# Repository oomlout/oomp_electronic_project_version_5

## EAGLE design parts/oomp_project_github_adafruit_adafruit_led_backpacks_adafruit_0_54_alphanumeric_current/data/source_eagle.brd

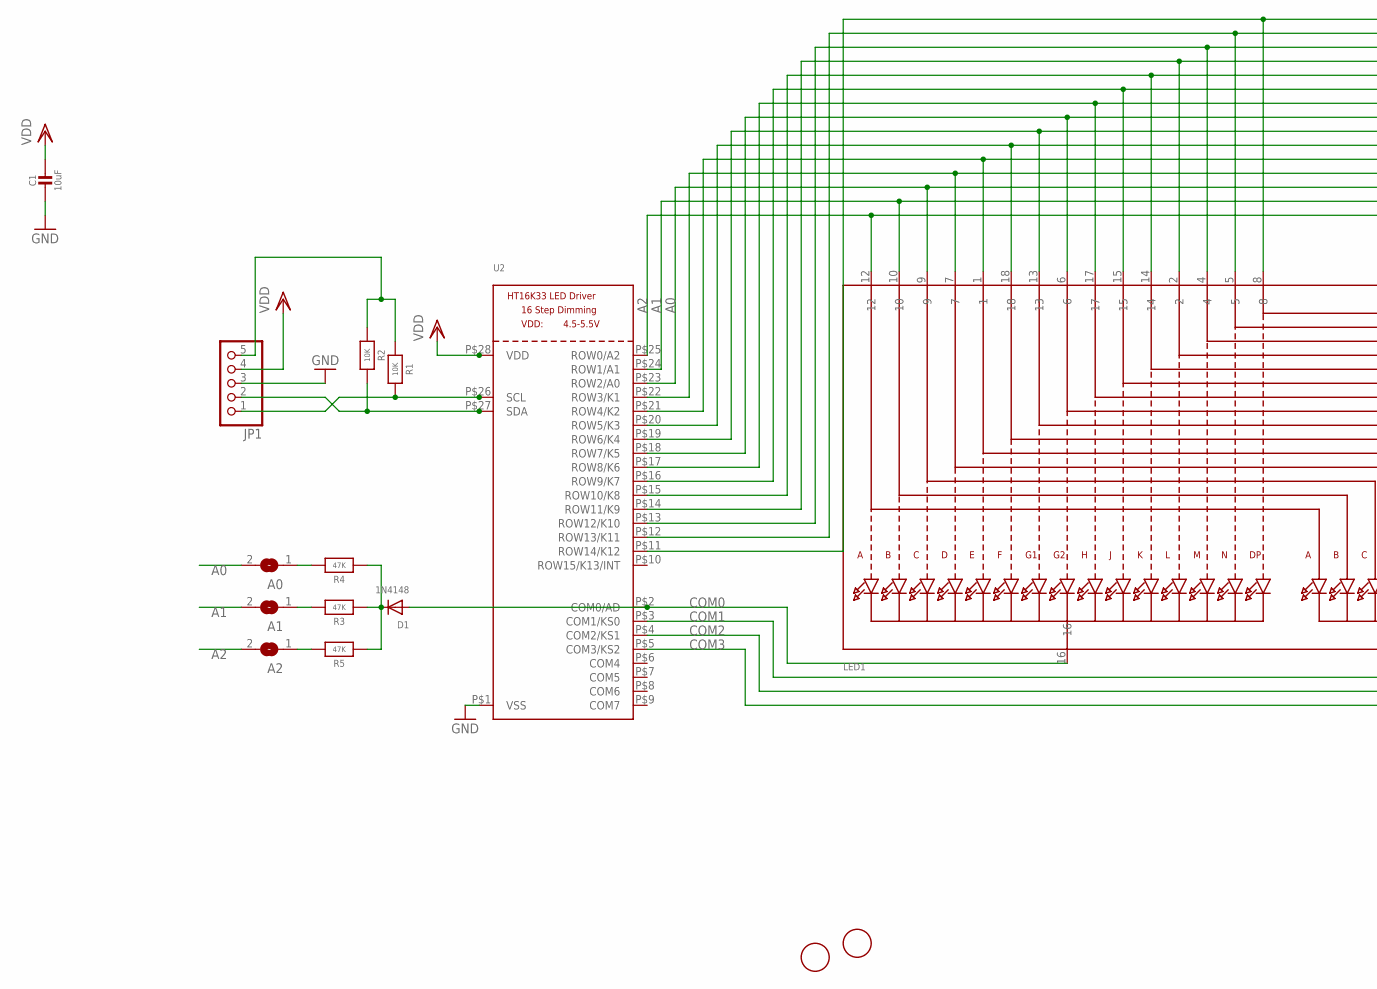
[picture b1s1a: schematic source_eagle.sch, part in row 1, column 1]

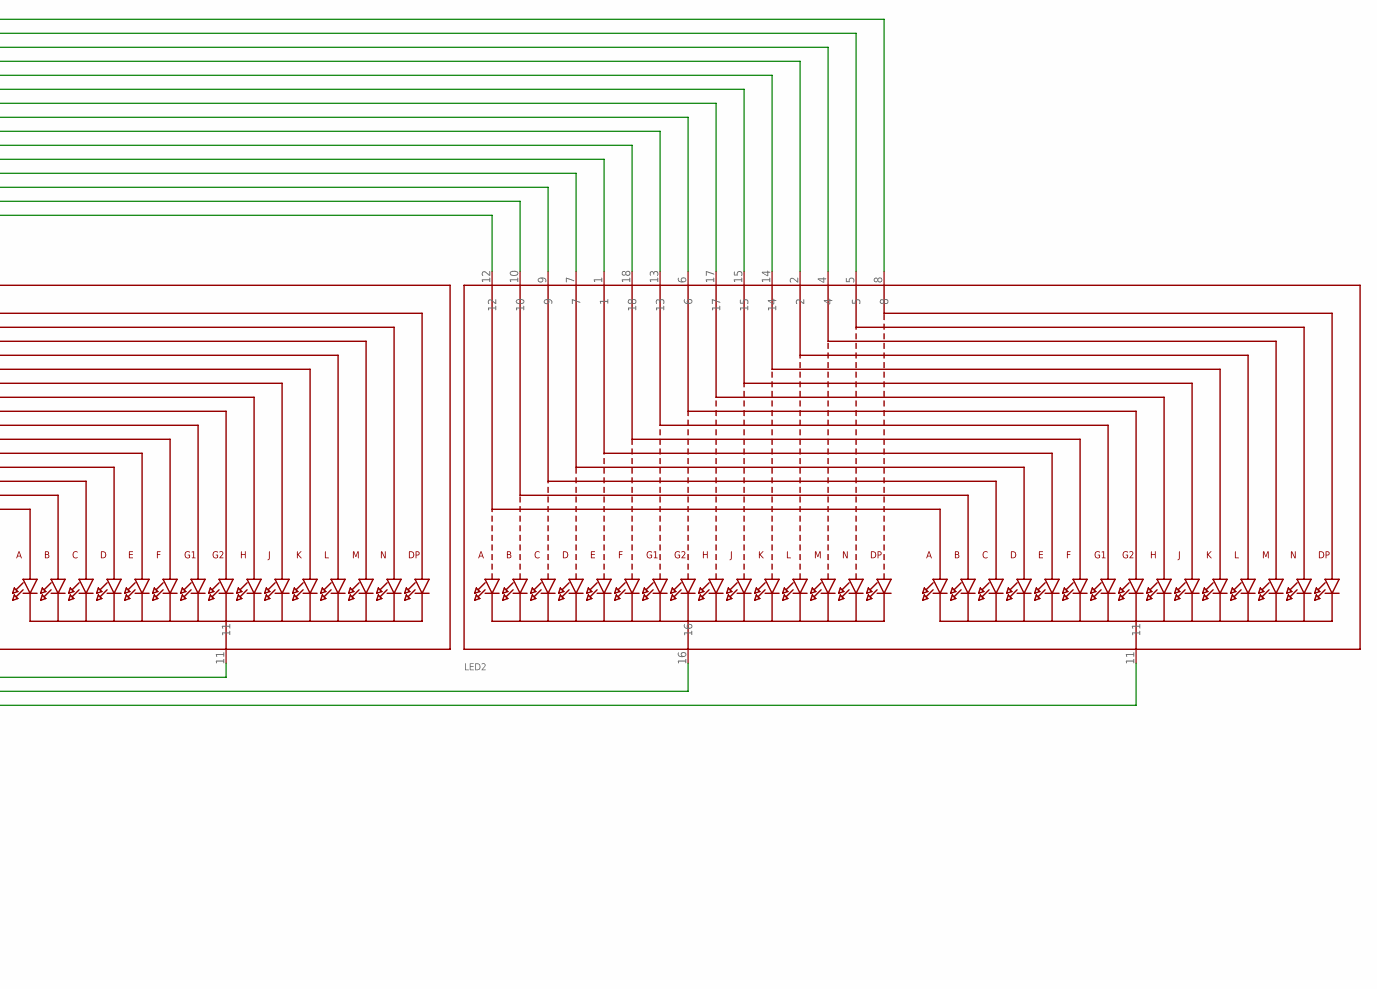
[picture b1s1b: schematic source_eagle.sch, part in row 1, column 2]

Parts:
A0, A1, A2: SOLDERJUMPERREFLOW_NOPASTE; SOLDERJUMPER_REFLOW_NOPASTE
C1: 10uF; 0805-NO
D1: 1N4148; SOD-323F
JP1: HEADER-1X570MIL; 1X05_ROUND_70
LED1, LED2: DISP_SEGMENT_STARBURST_DUAL_COMMONCATHODE; SEGMENT_STARTBUST_DUAL_KWA-541CBB
R1, R2: 10K; 0805-NO
R3, R4, R5: 47K; 0805-NO
U2: HT16K33_SOP28; SOP28_300MIL
U$1, U$2: FIDUCIAL; FIDUCIAL_1MM

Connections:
A0: A0.2, LED1.9, LED2.9, U2.P$23 (ROW2/A0)
A1: A1.2, LED1.10, LED2.10, U2.P$24 (ROW1/A1)
A2: A2.2, LED1.12, LED2.12, U2.P$25 (ROW0/A2)
COM0: D1.A, LED1.16, U2.P$2 (COM0/AD)
COM1: LED1.11, U2.P$3 (COM1/KS0)
COM2: LED2.16, U2.P$4 (COM2/KS1)
COM3: LED2.11, U2.P$5 (COM3/KS2)
GND: C1.2, JP1.3, U2.P$1 (VSS)
unnamed: D1.C, R3.1, R4.1, R5.1
unnamed: JP1.5, R1.1, R2.1
unnamed: LED1.17, LED2.17, U2.P$17 (ROW8/K6)
unnamed: LED1.15, LED2.15, U2.P$16 (ROW9/K7)
unnamed: LED1.14, LED2.14, U2.P$15 (ROW10/K8)
unnamed: A2.1, R5.2
unnamed: LED1.2, LED2.2, U2.P$14 (ROW11/K9)
unnamed: LED1.4, LED2.4, U2.P$13 (ROW12/K10)
unnamed: LED1.7, LED2.7, U2.P$22 (ROW3/K1)
unnamed: LED1.1, LED2.1, U2.P$21 (ROW4/K2)
unnamed: LED1.18, LED2.18, U2.P$20 (ROW5/K3)
unnamed: LED1.13, LED2.13, U2.P$19 (ROW6/K4)
unnamed: LED1.5, LED2.5, U2.P$12 (ROW13/K11)
unnamed: LED1.8, LED2.8, U2.P$11 (ROW14/K12)
unnamed: LED1.6, LED2.6, U2.P$18 (ROW7/K5)
unnamed: A1.1, R3.2
unnamed: A0.1, R4.2
SCL: JP1.1, R1.2, U2.P$26 (SCL)
SDA: JP1.2, R2.2, U2.P$27 (SDA)
VDD: C1.1, JP1.4, U2.P$28 (VDD)

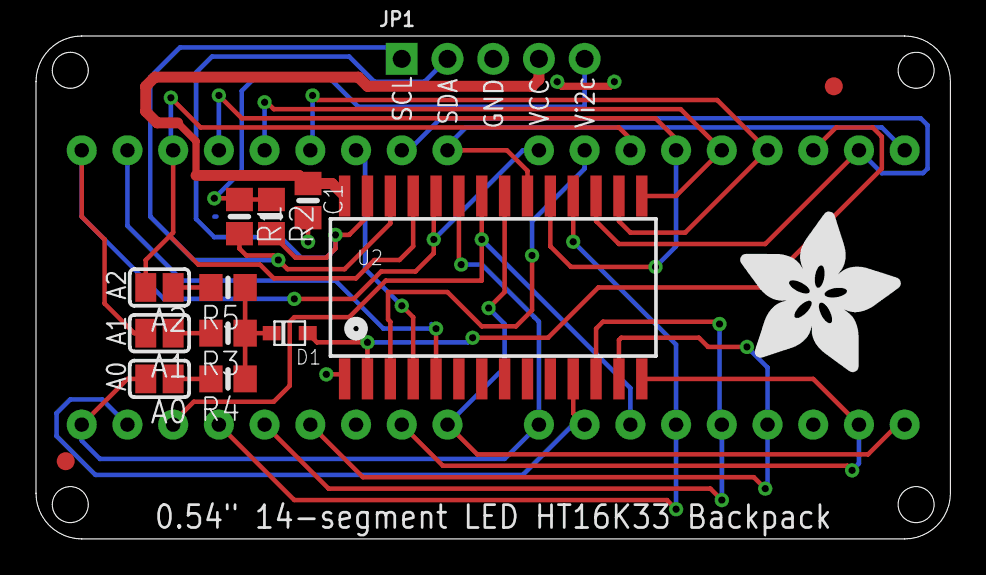
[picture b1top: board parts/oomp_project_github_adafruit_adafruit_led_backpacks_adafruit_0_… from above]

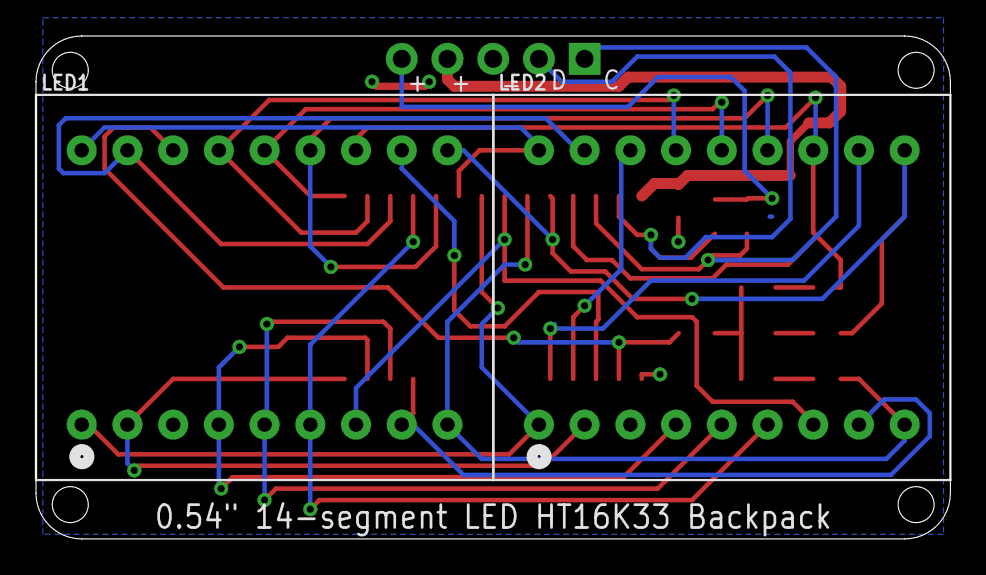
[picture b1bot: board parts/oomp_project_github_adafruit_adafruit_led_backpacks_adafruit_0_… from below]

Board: 2 copper layers, 50.8 x 27.9 mm, 17 parts (2 on the bottom side), 28 nets.

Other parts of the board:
U$3: ADAFRUIT_9MM

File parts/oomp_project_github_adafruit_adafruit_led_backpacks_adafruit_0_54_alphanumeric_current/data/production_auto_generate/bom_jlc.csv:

Comment,Designator,Footprint,LCSC Part #
,JP1,Adafruit 0.54 Alphanumeric v0.1-import-fps:1X05_ROUND_70,C42431835
,U$3,Adafruit 0.54 Alphanumeric v0.1-import-fps:ADAFRUIT_9MM,
,"LED1,LED2",Adafruit 0.54 Alphanumeric v0.1-import-fps:SEGMENT_STARTBUST_DUAL_KWA-541CBB,
,"A0,A1,A2",Adafruit 0.54 Alphanumeric v0.1-import-fps:SOLDERJUMPER_REFLOW_NOPASTE,
,U2,Adafruit 0.54 Alphanumeric v0.1-import-fps:SOP28_300MIL,
10K,"R1,R2",Adafruit 0.54 Alphanumeric v0.1-import-fps:0805-NO,C17414
10uF,C1,Adafruit 0.54 Alphanumeric v0.1-import-fps:0805-NO,
1N4148,D1,Adafruit 0.54 Alphanumeric v0.1-import-fps:SOD-323F,
47K,"R3,R4,R5",Adafruit 0.54 Alphanumeric v0.1-import-fps:0805-NO,C17713
FIDUCIAL,"U$1,U$2",Adafruit 0.54 Alphanumeric v0.1-import-fps:FIDUCIAL_1MM,

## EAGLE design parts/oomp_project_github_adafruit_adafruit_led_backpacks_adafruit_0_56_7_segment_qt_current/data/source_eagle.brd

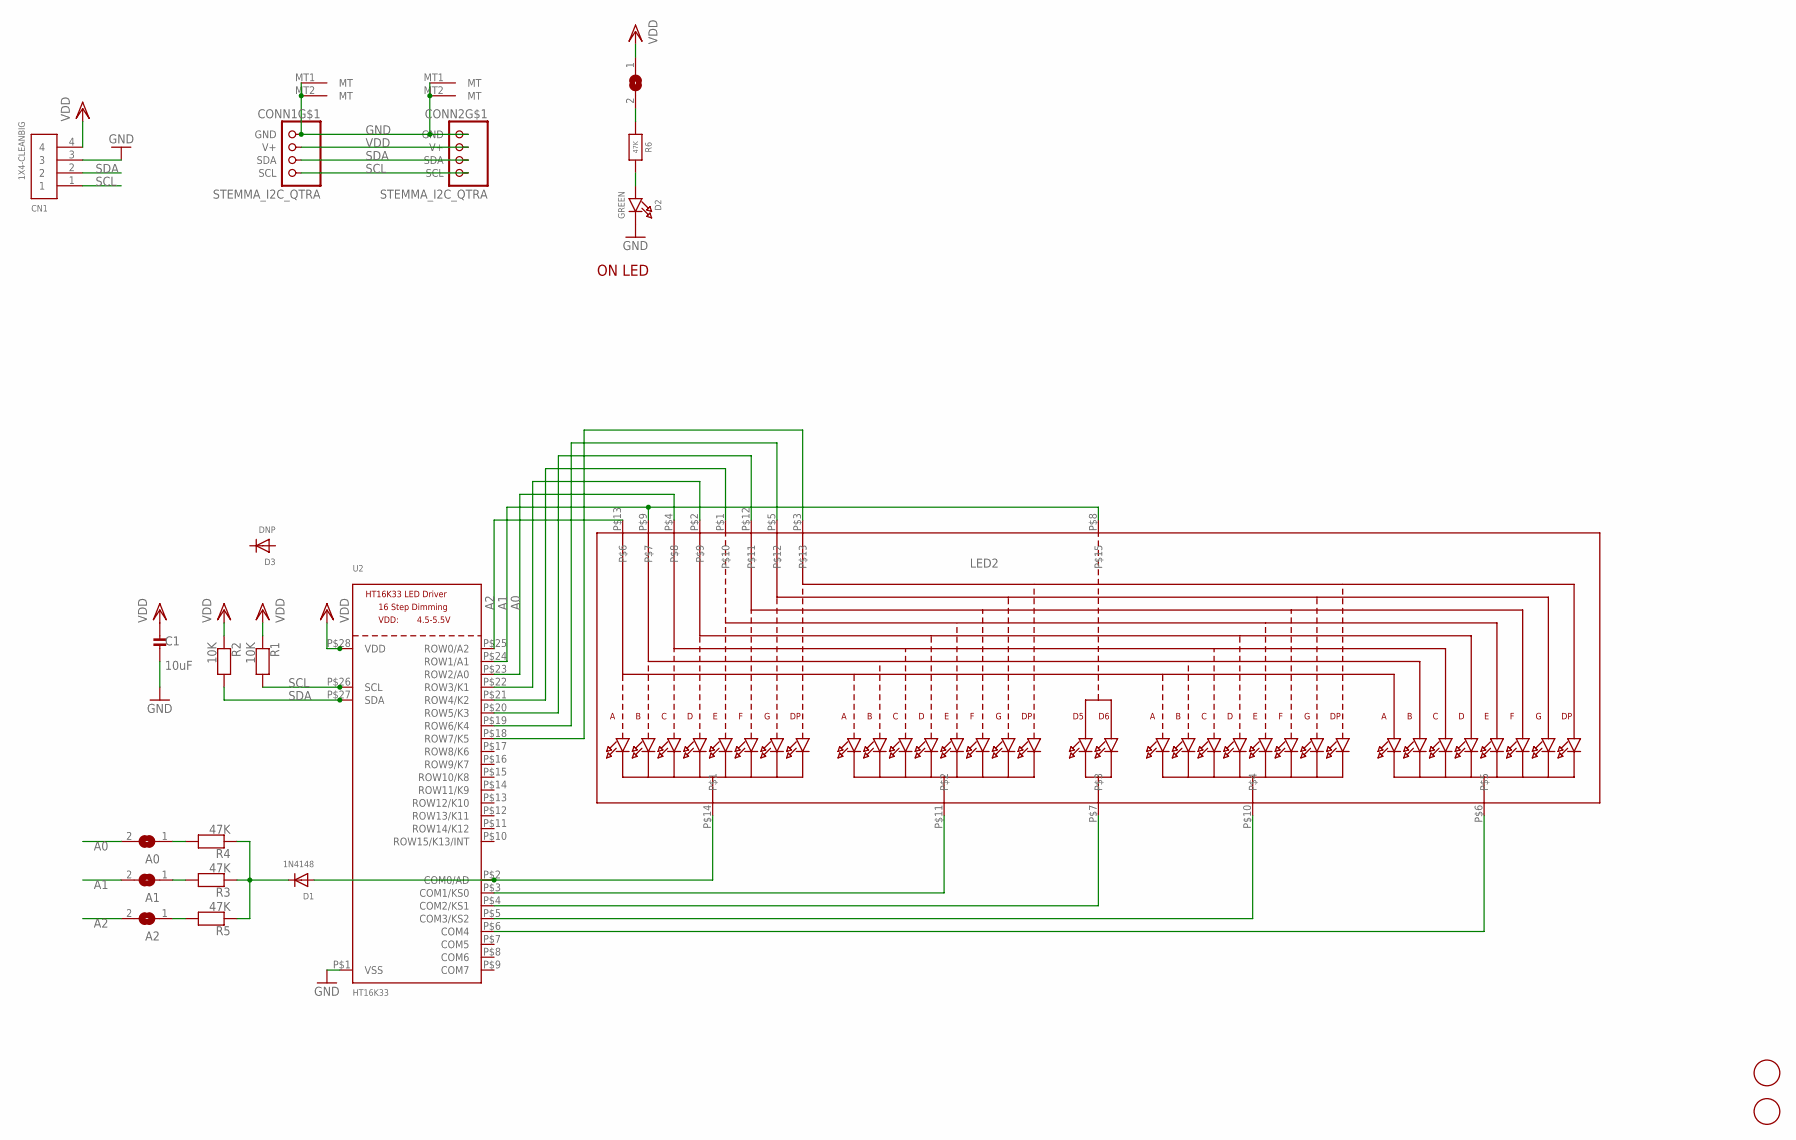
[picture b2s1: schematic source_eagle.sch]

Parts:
A0, A1, A2: SOLDERJUMPER; SOLDERJUMPER_ARROW_NOPASTE
C1: 10uF; 0805_10MGAP
CN1: 1X4-CLEANBIG; 1X04-CLEANBIG
CONN1, CONN2: STEMMA_I2C_QTRA; JST_SH4_RA
D1: 1N4148; SOD-323F
D2: GREEN; CHIPLED_0603_NOOUTLINE
D3: DNP; SOD-323F
LED2: DISP_SEGMENT_4DIGIT_BL-Q56C43; SEGMENT-BL-Q56C43
LEDJMP: SOLDERJUMPERCLOSED; SOLDERJUMPER_CLOSEDWIRE
R1, R2: 10K; 0603-NO
R3, R4, R5, R6: 47K; 0603-NO
U2: HT16K33; SOP28_300MIL_SKINNY
U$1, U$2: FIDUCIAL; FIDUCIAL_1MM

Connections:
A0: A0.2, LED2.P$4, U2.P$23 (ROW2/A0)
A1: A1.2, LED2.P$8, LED2.P$9, U2.P$24 (ROW1/A1)
A2: A2.2, LED2.P$13, U2.P$25 (ROW0/A2)
GND: C1.2, CN1.3, CONN1.1 (GND), CONN1.MT1 (MT), CONN1.MT2 (MT), CONN2.1 (GND), CONN2.MT1 (MT), CONN2.MT2 (MT), D2.C, U2.P$1 (VSS)
unnamed: D1.C, R3.1, R4.1, R5.1
unnamed: D1.A, LED2.P$14, U2.P$2 (COM0/AD)
unnamed: LED2.P$11, U2.P$3 (COM1/KS0)
unnamed: LED2.P$7, U2.P$4 (COM2/KS1)
unnamed: LED2.P$10, U2.P$5 (COM3/KS2)
unnamed: LED2.P$6, U2.P$6 (COM4)
unnamed: A2.1, R5.2
unnamed: D2.A, R6.2
unnamed: LEDJMP.2, R6.1
unnamed: LED2.P$2, U2.P$22 (ROW3/K1)
unnamed: LED2.P$1, U2.P$21 (ROW4/K2)
unnamed: LED2.P$12, U2.P$20 (ROW5/K3)
unnamed: LED2.P$5, U2.P$19 (ROW6/K4)
unnamed: LED2.P$3, U2.P$18 (ROW7/K5)
unnamed: A1.1, R3.2
unnamed: A0.1, R4.2
SCL: CN1.1, CONN1.4 (SCL), CONN2.4 (SCL), R1.2, U2.P$26 (SCL)
SDA: CN1.2, CONN1.3 (SDA), CONN2.3 (SDA), R2.2, U2.P$27 (SDA)
VDD: C1.1, CN1.4, CONN1.2 (V+), CONN2.2 (V+), LEDJMP.1, R1.1, R2.1, U2.P$28 (VDD)

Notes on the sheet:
ON LED

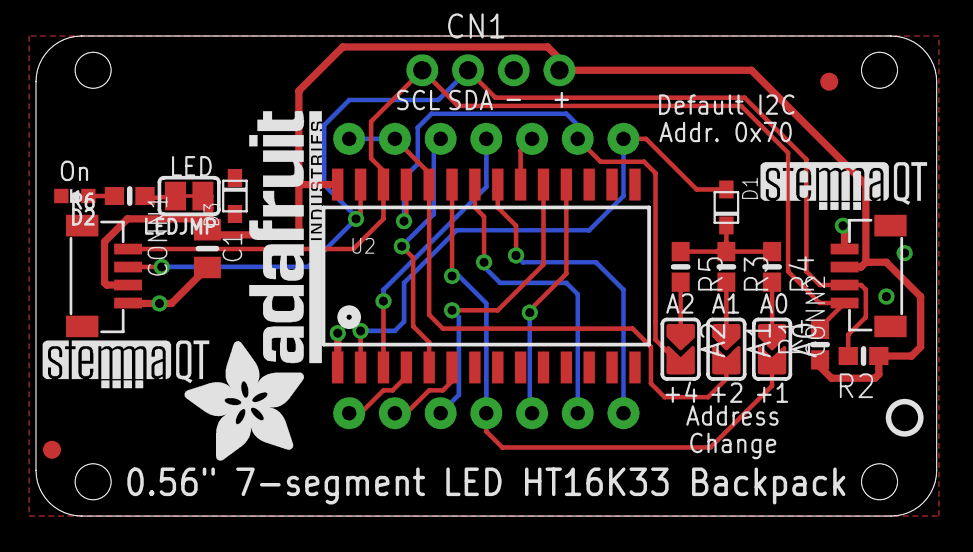
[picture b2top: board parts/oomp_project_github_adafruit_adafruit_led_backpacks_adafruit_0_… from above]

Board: 2 copper layers, 50.0 x 26.7 mm, 25 parts (1 on the bottom side), 23 nets.

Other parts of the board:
U$3: ADAFRUIT_TEXT_20MM
U$5, U$6: STEMMAQT
U$7: PCBFEAT-REV-040

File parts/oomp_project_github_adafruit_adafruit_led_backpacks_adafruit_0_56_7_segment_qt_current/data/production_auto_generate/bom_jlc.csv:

Comment,Designator,Footprint,LCSC Part #
,U$3,Adafruit 0.56 7-Segment QT-import-fps:ADAFRUIT_TEXT_20MM,
,U$7,Adafruit 0.56 7-Segment QT-import-fps:PCBFEAT-REV-040,
,"A0,A1,A2",Adafruit 0.56 7-Segment QT-import-fps:SOLDERJUMPER_ARROW_NOPASTE,
,LEDJMP0,Adafruit 0.56 7-Segment QT-import-fps:SOLDERJUMPER_CLOSEDWIRE,
,"U$5,U$6",Adafruit 0.56 7-Segment QT-import-fps:STEMMAQT,
10K,"R1,R2",Adafruit 0.56 7-Segment QT-import-fps:0603-NO,C98220
10uF,C1,Adafruit 0.56 7-Segment QT-import-fps:0805_10MGAP,
1N4148,D1,Adafruit 0.56 7-Segment QT-import-fps:SOD-323F,
1X4-CLEANBIG,CN1,Adafruit 0.56 7-Segment QT-import-fps:1X04-CLEANBIG,
47K,"R3,R4,R5,R6",Adafruit 0.56 7-Segment QT-import-fps:0603-NO,C2907042
DNP,D3,Adafruit 0.56 7-Segment QT-import-fps:SOD-323F,
FIDUCIAL,"U$1,U$2",Adafruit 0.56 7-Segment QT-import-fps:FIDUCIAL_1MM,
GREEN,D2,Adafruit 0.56 7-Segment QT-import-fps:CHIPLED_0603_NOOUTLINE,
HT16K33,U2,Adafruit 0.56 7-Segment QT-import-fps:SOP28_300MIL_SKINNY,
STEMMA_I2C_QTRA,"CONN1,CONN2",Adafruit 0.56 7-Segment QT-import-fps:JST_SH4_RA,

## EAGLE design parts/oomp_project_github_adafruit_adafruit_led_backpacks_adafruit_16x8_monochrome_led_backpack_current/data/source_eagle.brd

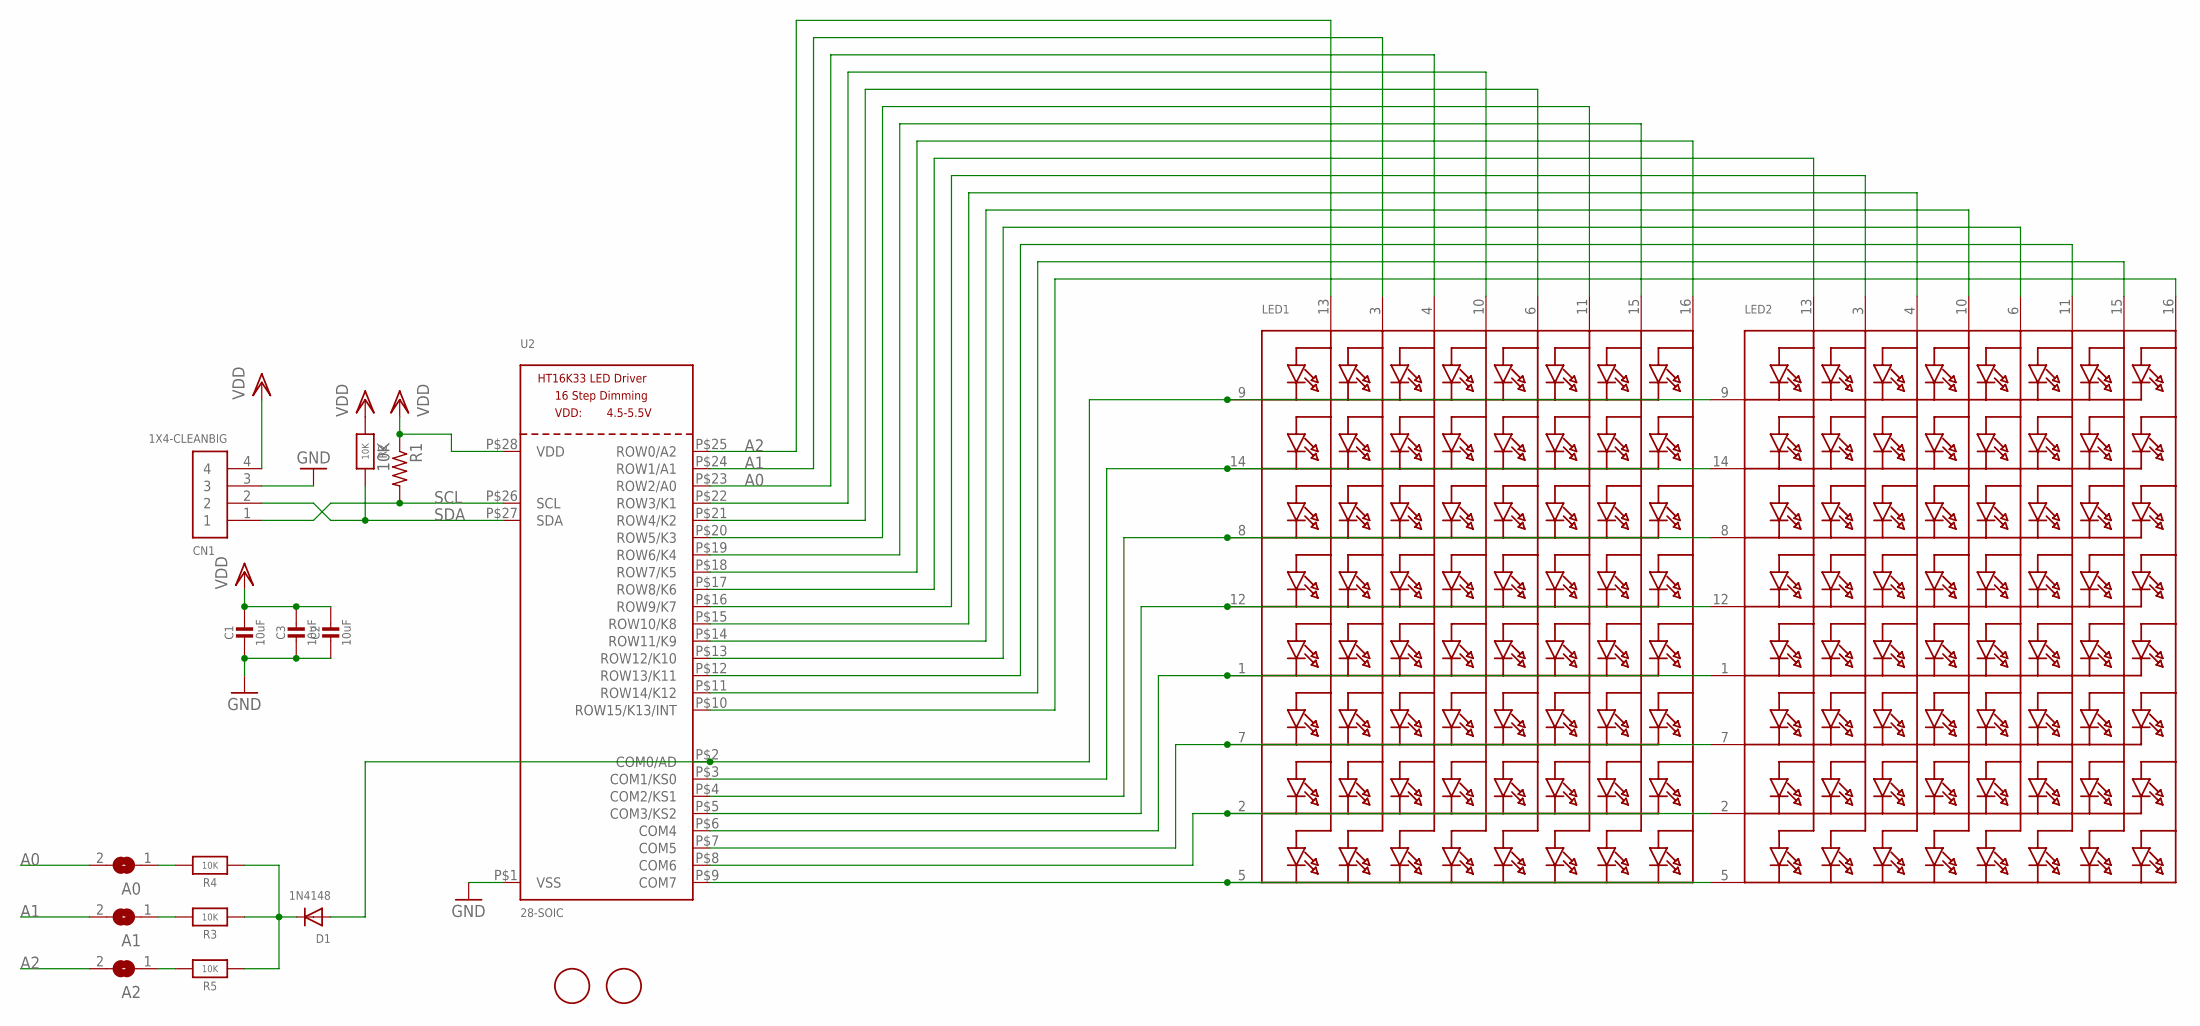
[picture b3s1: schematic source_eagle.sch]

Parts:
A0, A1, A2: SOLDERJUMPERREFLOW_NOPASTE; SOLDERJUMPER_REFLOW_NOPASTE
C1, C2, C3: 10uF; 0805-NO
CN1: 1X4-CLEANBIG; 1X04-CLEANBIG
D1: 1N4148; SOD-323F
LED1, LED2: DISP_SEGMENT_8X8_ROWCATHODEM12A881UR; SEGMENT_BL-M12A881UR
R1: 10K; R0805
R2, R3, R4, R5: 10K; 0805-NO
U2: 28-SOIC; SOP28_300MIL
U$1, U$2: FIDUCIAL; FIDUCIAL_1MM

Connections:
A0: A0.2, LED1.4 (A3), U2.P$23 (ROW2/A0)
A1: A1.2, LED1.3 (A2), U2.P$24 (ROW1/A1)
A2: A2.2, LED1.13 (A1), U2.P$25 (ROW0/A2)
GND: C1.2, C2.2, C3.2, CN1.3, U2.P$1 (VSS)
unnamed: LED1.5 (K8), LED2.5 (K8), U2.P$9 (COM7)
unnamed: LED1.2 (K7), LED2.2 (K7), U2.P$8 (COM6)
unnamed: LED1.7 (K6), LED2.7 (K6), U2.P$7 (COM5)
unnamed: LED1.1 (K5), LED2.1 (K5), U2.P$6 (COM4)
unnamed: LED1.12 (K4), LED2.12 (K4), U2.P$5 (COM3/KS2)
unnamed: LED1.8 (K3), LED2.8 (K3), U2.P$4 (COM2/KS1)
unnamed: LED1.14 (K2), LED2.14 (K2), U2.P$3 (COM1/KS0)
unnamed: D1.A, LED1.9 (K1), LED2.9 (K1), U2.P$2 (COM0/AD)
unnamed: A2.1, R5.2
unnamed: LED2.15 (A7), U2.P$11 (ROW14/K12)
unnamed: LED2.11 (A6), U2.P$12 (ROW13/K11)
unnamed: LED2.16 (A8), U2.P$10 (ROW15/K13/INT)
unnamed: D1.C, R3.1, R4.1, R5.1
unnamed: A1.1, R3.2
unnamed: A0.1, R4.2
unnamed: LED1.16 (A8), U2.P$18 (ROW7/K5)
unnamed: LED1.15 (A7), U2.P$19 (ROW6/K4)
unnamed: LED1.6 (A5), U2.P$21 (ROW4/K2)
unnamed: LED1.10 (A4), U2.P$22 (ROW3/K1)
unnamed: LED1.11 (A6), U2.P$20 (ROW5/K3)
unnamed: LED2.13 (A1), U2.P$17 (ROW8/K6)
unnamed: LED2.3 (A2), U2.P$16 (ROW9/K7)
unnamed: LED2.10 (A4), U2.P$14 (ROW11/K9)
unnamed: LED2.4 (A3), U2.P$15 (ROW10/K8)
unnamed: LED2.6 (A5), U2.P$13 (ROW12/K10)
SCL: CN1.1, R1.2, U2.P$26 (SCL)
SDA: CN1.2, R2.2, U2.P$27 (SDA)
VDD: C1.1, C2.1, C3.1, CN1.4, R1.1, R2.1, U2.P$28 (VDD)

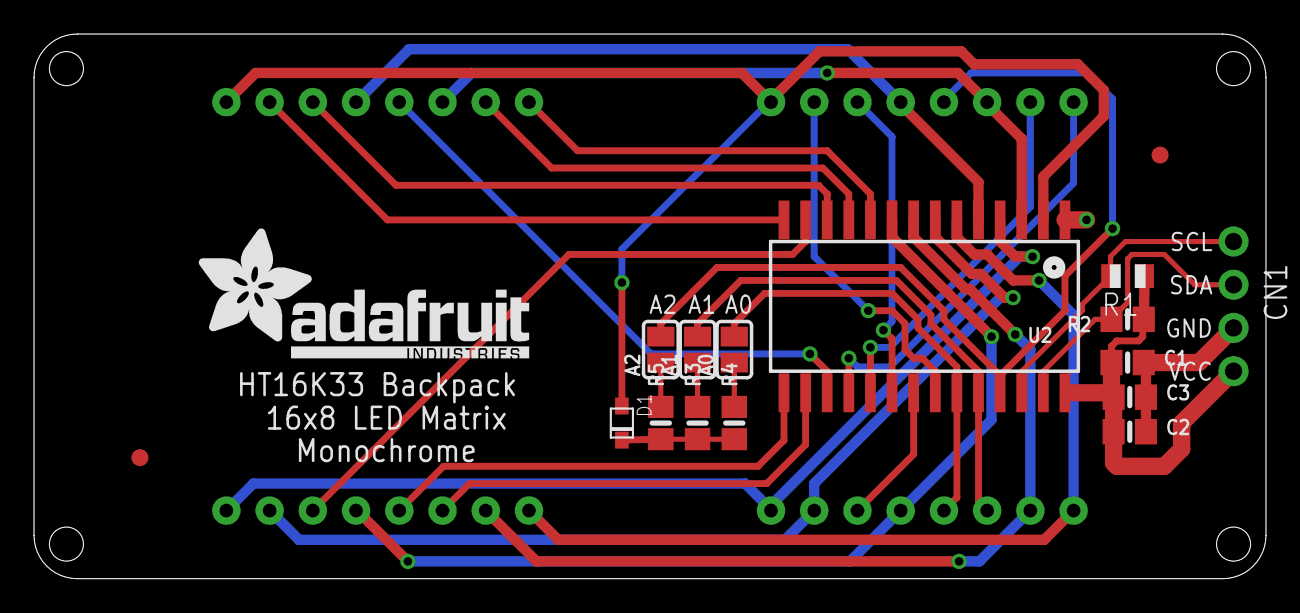
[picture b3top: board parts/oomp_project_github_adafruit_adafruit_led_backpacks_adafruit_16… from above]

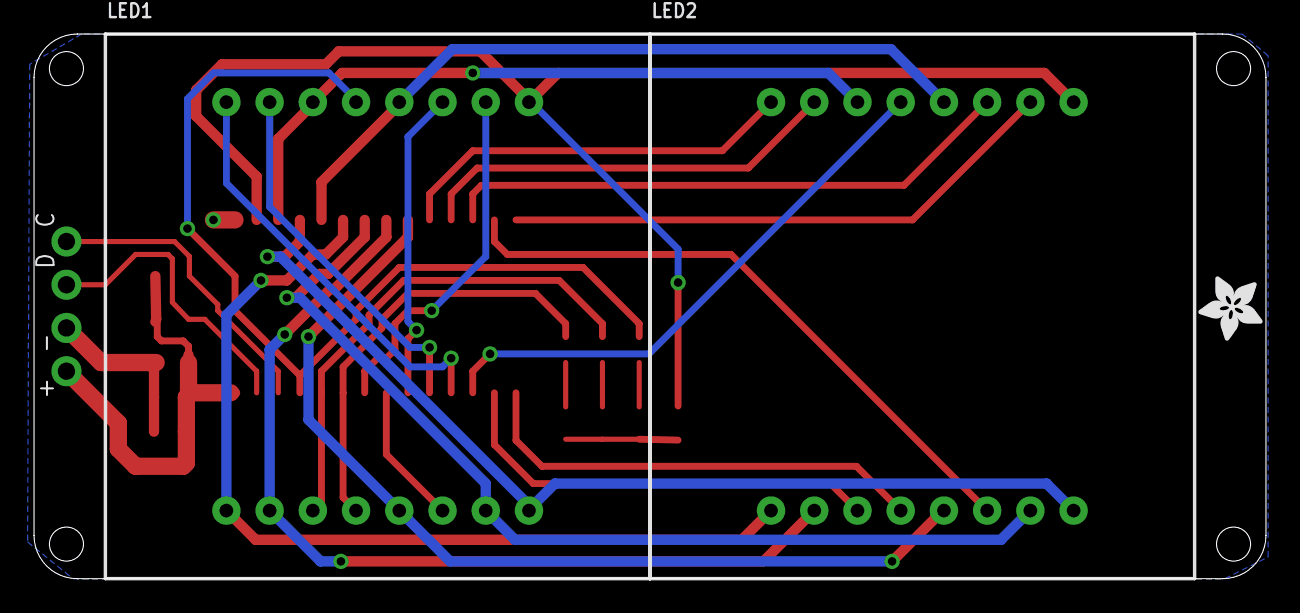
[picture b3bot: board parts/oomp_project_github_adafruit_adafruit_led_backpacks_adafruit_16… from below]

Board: 2 copper layers, 72.4 x 32.0 mm, 20 parts (3 on the bottom side), 32 nets.

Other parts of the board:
U$3: ADAFRUIT_TEXT_20MM
U$4: ADAFRUIT_3.5MM

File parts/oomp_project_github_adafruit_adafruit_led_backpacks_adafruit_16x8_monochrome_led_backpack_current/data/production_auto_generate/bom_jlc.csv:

Comment,Designator,Footprint,LCSC Part #
,U$4,Adafruit 16x8 Monochrome LED Backpack-import-fps:ADAFRUIT_3.5MM,
,U$3,Adafruit 16x8 Monochrome LED Backpack-import-fps:ADAFRUIT_TEXT_20MM,
,"LED1,LED2",Adafruit 16x8 Monochrome LED Backpack-import-fps:SEGMENT_BL-M12A881UR,
,"A0,A1,A2",Adafruit 16x8 Monochrome LED Backpack-import-fps:SOLDERJUMPER_REFLOW_NOPASTE,
10K,"R2,R3,R4,R5",Adafruit 16x8 Monochrome LED Backpack-import-fps:0805-NO,C17414
10K,R1,Adafruit 16x8 Monochrome LED Backpack-import-fps:R0805,C17414
10uF,"C1,C2,C3",Adafruit 16x8 Monochrome LED Backpack-import-fps:0805-NO,
1N4148,D1,Adafruit 16x8 Monochrome LED Backpack-import-fps:SOD-323F,
1X4-CLEANBIG,CN1,Adafruit 16x8 Monochrome LED Backpack-import-fps:1X04-CLEANBIG,
28-SOIC,U2,Adafruit 16x8 Monochrome LED Backpack-import-fps:SOP28_300MIL,
FIDUCIAL,"U$1,U$2",Adafruit 16x8 Monochrome LED Backpack-import-fps:FIDUCIAL_1MM,

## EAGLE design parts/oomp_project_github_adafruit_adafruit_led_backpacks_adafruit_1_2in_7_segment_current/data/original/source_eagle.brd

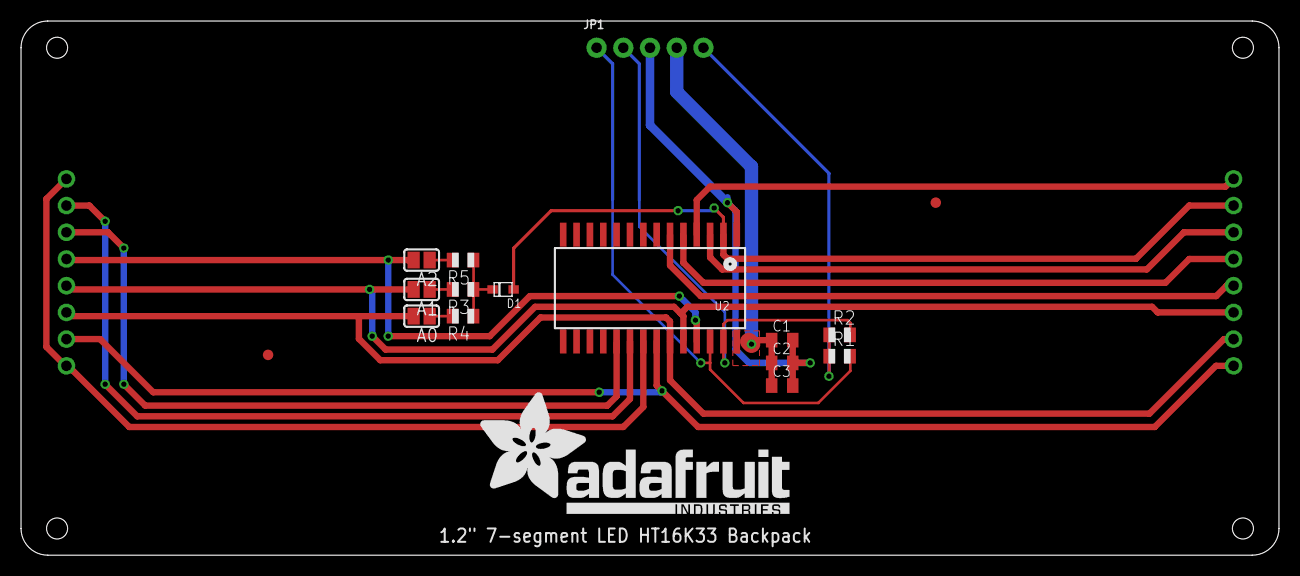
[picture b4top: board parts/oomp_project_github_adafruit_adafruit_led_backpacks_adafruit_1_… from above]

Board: 2 copper layers, 119.6 x 50.8 mm, 18 parts (1 on the bottom side), 21 nets.

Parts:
A0, A1, A2: SOLDERJUMPER_REFLOW_NOPASTE
C1, C2, C3: 10uF; C0805K
D1: 1N4148; SOD-323F
JP1: 1X05_ROUND_76
LED1: BL-Q120X-41; SEGMENT_BL-Q120A
R1, R2: 10K; R0805
R3, R4, R5: 47K; R0805
U2: SOP28_300MIL
U$1, U$2: FIDUCIAL; FIDUCIAL_1MM
U$3: ADAFRUIT_TEXT_30MM

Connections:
A0: A0.2, LED1.7, LED1.11, U2.P$23
A1: A1.2, LED1.6, LED1.12, U2.P$24
A2: A2.2, LED1.13, U2.P$25
GND: C1.2, C2.2, C3.2, JP1.3, U2.P$1
unnamed: D1.C, R3.1, R4.1, R5.1
unnamed: D1.A, LED1.1, U2.P$2
unnamed: LED1.3, U2.P$3
unnamed: LED1.4, U2.P$5
unnamed: LED1.5, U2.P$6
unnamed: LED1.2, U2.P$4
unnamed: A2.1, R5.2
unnamed: JP1.5, R1.1, R2.1
unnamed: LED1.8, LED1.10, U2.P$22
unnamed: LED1.9, LED1.16, U2.P$21
unnamed: LED1.15, U2.P$20
unnamed: LED1.14, U2.P$19
unnamed: A1.1, R3.2
unnamed: A0.1, R4.2
SCL: JP1.1, R1.2, U2.P$26
SDA: JP1.2, R2.2, U2.P$27
VDD: C1.1, C2.1, C3.1, JP1.4, U2.P$28

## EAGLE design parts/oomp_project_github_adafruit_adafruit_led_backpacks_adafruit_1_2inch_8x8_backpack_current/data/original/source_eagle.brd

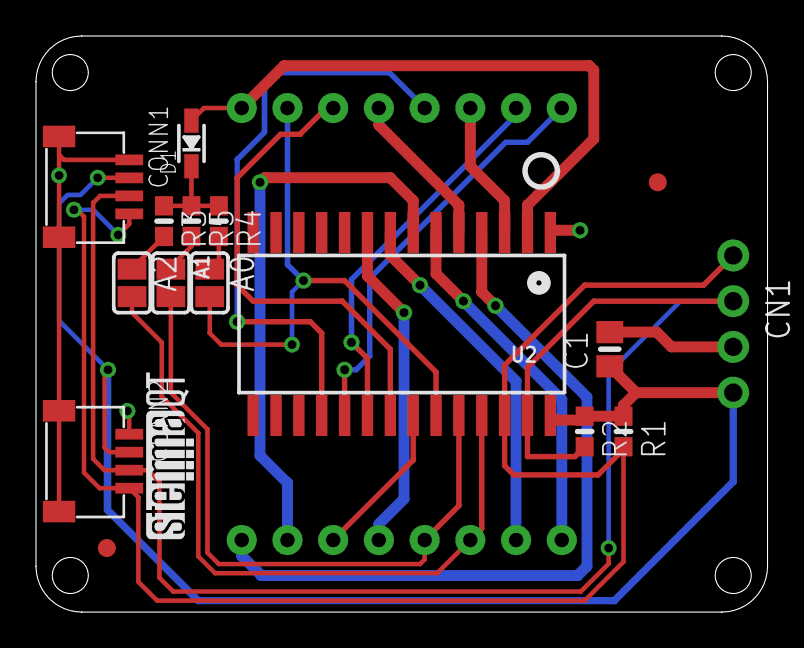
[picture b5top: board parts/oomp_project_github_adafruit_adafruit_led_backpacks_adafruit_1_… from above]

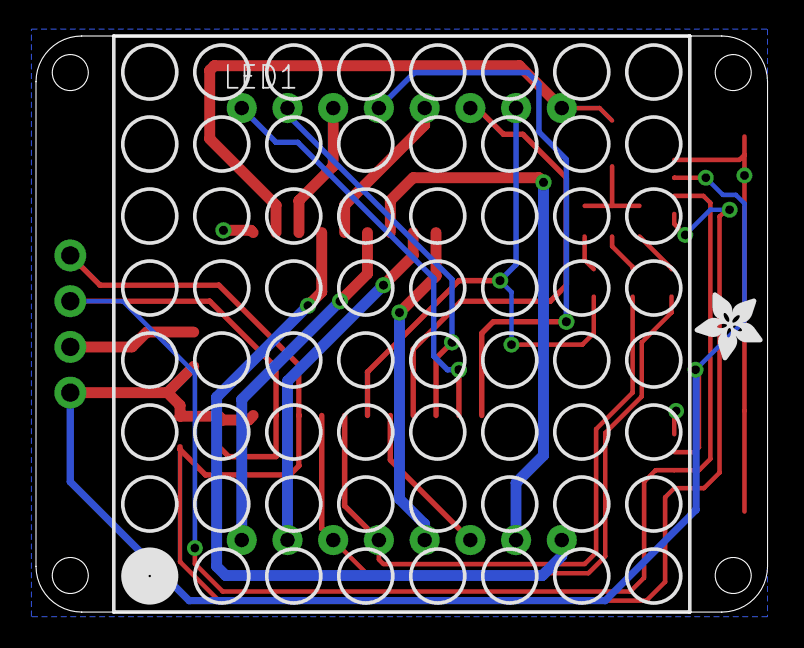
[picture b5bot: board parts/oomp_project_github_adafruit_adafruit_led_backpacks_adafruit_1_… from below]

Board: 2 copper layers, 40.6 x 32.0 mm, 34 parts (6 on the bottom side), 24 nets.

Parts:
A0, A1, A2: SOLDERJUMPER_REFLOW_NOPASTE
C1: 10uF; 0805-NO
CN1: 1X4-CLEANBIG; 1X04-CLEANBIG
CONN1, CONN2: STEMMA_I2C_QT; JST_SH4
D1: 1N4148; SOD-323
LED1: BL-M07C881UR; SEGMENT_BL-M12A881UR
PLABEL0: PLABEL0
PLABEL1: PLABEL1
PLABEL2: PLABEL2
PLABEL3: PLABEL3
PLABEL4: PLABEL4
PLABEL5: PLABEL5
PLABEL6: PLABEL6
PLABEL7: PLABEL7
PLABEL8: PLABEL8
PLABEL9: PLABEL9
PLABEL10: PLABEL10
PLABEL11: PLABEL11
PLABEL12: PLABEL12
PLABEL13: PLABEL13
R1, R2, R3, R4, R5: 10K; 0603-NO
U2: HT16K33; SOP28_300MIL
U$1, U$2: FIDUCIAL; FIDUCIAL_1MM
U$3: ADAFRUIT_3.5MM
U$4: PCBFEAT-REV-040
U$5: STEMMAQT

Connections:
A0: A0.2, LED1.10, U2.P$23
A1: A1.2, LED1.4, U2.P$24
A2: A2.2, LED1.3, U2.P$25
GND: C1.2, CN1.3, CONN1.1, CONN1.MT1, CONN1.MT2, CONN2.1, CONN2.MT1, CONN2.MT2, U2.P$1
unnamed: LED1.5, U2.P$9
unnamed: LED1.2, U2.P$8
unnamed: LED1.7, U2.P$7
unnamed: LED1.1, U2.P$6
unnamed: LED1.12, U2.P$5
unnamed: LED1.8, U2.P$4
unnamed: LED1.14, U2.P$3
unnamed: D1.A, LED1.9, U2.P$2
unnamed: A1.1, R5.2
unnamed: LED1.6, U2.P$22
unnamed: LED1.11, U2.P$21
unnamed: D1.C, R3.1, R4.1, R5.1
unnamed: LED1.13, U2.P$18
unnamed: A2.1, R3.2
unnamed: A0.1, R4.2
SCL: CN1.1, CONN1.4, CONN2.4, R1.2, U2.P$26
SDA: CN1.2, CONN1.3, CONN2.3, R2.2, U2.P$27
SEG_F: LED1.15, U2.P$20
SEG_G: LED1.16, U2.P$19
VDD: C1.1, CN1.4, CONN1.2, CONN2.2, R1.1, R2.1, U2.P$28

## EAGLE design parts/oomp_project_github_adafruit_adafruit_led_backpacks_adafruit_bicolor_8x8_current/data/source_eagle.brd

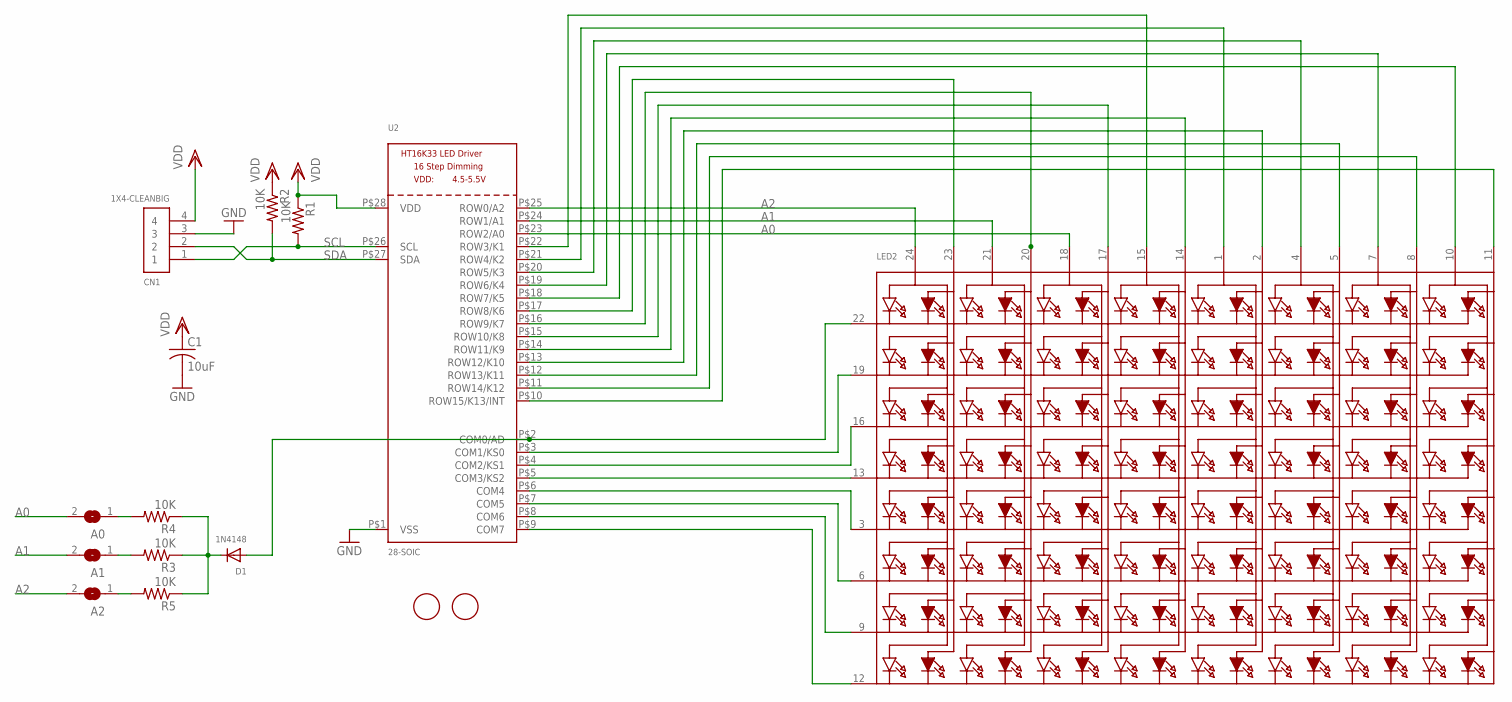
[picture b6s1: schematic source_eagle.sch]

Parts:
A0, A1, A2: SOLDERJUMPERREFLOW_NOPASTE; SOLDERJUMPER_REFLOW_NOPASTE
C1: 10uF; C0805
CN1: 1X4-CLEANBIG; 1X04-CLEANBIG
D1: 1N4148; SOD-323F
LED2: DISP_SEGMENT_8X8_BICOLOR_ROWCATHODEMI2A883XX; SEGMENT_BICOL_BL-M12A883XX
R1, R2, R3, R4, R5: 10K; R0805
U2: 28-SOIC; SOP28_300MIL
U$1, U$2: FIDUCIAL; FIDUCIAL_1MM

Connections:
A0: A0.2, LED2.18 (A5), U2.P$23 (ROW2/A0)
A1: A1.2, LED2.21 (A3), U2.P$24 (ROW1/A1)
A2: A2.2, LED2.24 (A1), U2.P$25 (ROW0/A2)
GND: C1.2, CN1.3, U2.P$1 (VSS)
unnamed: LED2.12 (K8), U2.P$9 (COM7)
unnamed: LED2.9 (K7), U2.P$8 (COM6)
unnamed: LED2.6 (K6), U2.P$7 (COM5)
unnamed: LED2.3 (K5), U2.P$6 (COM4)
unnamed: LED2.13 (K4), U2.P$5 (COM3/KS2)
unnamed: LED2.16 (K3), U2.P$4 (COM2/KS1)
unnamed: LED2.19 (K2), U2.P$3 (COM1/KS0)
unnamed: D1.A, LED2.22 (K1), U2.P$2 (COM0/AD)
unnamed: A2.1, R5.2
unnamed: LED2.8 (A14), U2.P$11 (ROW14/K12)
unnamed: LED2.5 (A12), U2.P$12 (ROW13/K11)
unnamed: LED2.11 (A16), U2.P$10 (ROW15/K13/INT)
unnamed: D1.C, R3.1, R4.1, R5.1
unnamed: A1.1, R3.2
unnamed: A0.1, R4.2
unnamed: LED2.10 (A15), U2.P$18 (ROW7/K5)
unnamed: LED2.7 (A13), U2.P$19 (ROW6/K4)
unnamed: LED2.1 (A9), U2.P$21 (ROW4/K2)
unnamed: LED2.15 (A7), U2.P$22 (ROW3/K1)
unnamed: LED2.4 (A11), U2.P$20 (ROW5/K3)
unnamed: LED2.23 (A2), U2.P$17 (ROW8/K6)
unnamed: LED2.20 (A4), U2.P$16 (ROW9/K7)
unnamed: LED2.14 (A8), U2.P$14 (ROW11/K9)
unnamed: LED2.17 (A6), U2.P$15 (ROW10/K8)
unnamed: LED2.2 (A10), U2.P$13 (ROW12/K10)
SCL: CN1.1, R1.2, U2.P$26 (SCL)
SDA: CN1.2, R2.2, U2.P$27 (SDA)
VDD: C1.1, CN1.4, R1.1, R2.1, U2.P$28 (VDD)

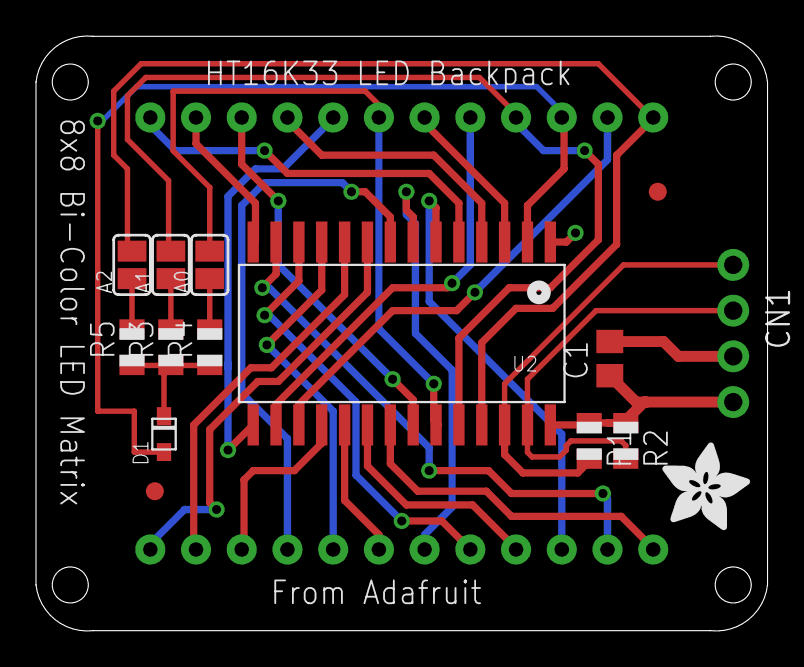
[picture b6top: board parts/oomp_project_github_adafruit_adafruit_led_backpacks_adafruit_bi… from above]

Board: 2 copper layers, 40.6 x 33.1 mm, 16 parts (1 on the bottom side), 32 nets.

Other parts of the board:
U$3: ADAFRUIT_5MM

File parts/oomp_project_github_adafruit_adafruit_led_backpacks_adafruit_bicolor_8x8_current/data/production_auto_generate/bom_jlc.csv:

Comment,Designator,Footprint,LCSC Part #
,U$3,Adafruit bicolor 8x8-import-fps:ADAFRUIT_5MM,
,LED2,Adafruit bicolor 8x8-import-fps:SEGMENT_BICOL_BL-M12A883XX,
,"A0,A1,A2",Adafruit bicolor 8x8-import-fps:SOLDERJUMPER_REFLOW_NOPASTE,
10K,"R1,R2,R3,R4,R5",Adafruit bicolor 8x8-import-fps:R0805,C17414
10uF,C1,Adafruit bicolor 8x8-import-fps:C0805,
1N4148,D1,Adafruit bicolor 8x8-import-fps:SOD-323F,
1X4-CLEANBIG,CN1,Adafruit bicolor 8x8-import-fps:1X04-CLEANBIG,
28-SOIC,U2,Adafruit bicolor 8x8-import-fps:SOP28_300MIL,
FIDUCIAL,"U$1,U$2",Adafruit bicolor 8x8-import-fps:FIDUCIAL_1MM,

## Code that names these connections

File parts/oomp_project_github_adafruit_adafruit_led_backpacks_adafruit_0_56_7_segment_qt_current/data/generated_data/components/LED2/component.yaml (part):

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      connected_to:
      - reference: U2
        pin_number: P$4
        pin_name: COM2/KS1
    - number: P$8
      name: P$15
      electrical_type: bidirectional
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      connected_to:
      - reference: U2
        pin_number: P$5
        pin_name: COM3/KS2
    - number: P$11
      name: P$2
      electrical_type: bidirectional
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      connected_to:
      - reference: U2
        pin_number: P$3
        pin_name: COM1/KS0
    - number: P$12
      name: P$11
      electrical_type: bidirectional
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        pin_name: A
      - reference: U2
        pin_number: P$2
        pin_name: COM0/AD
    size:
      local_graphics:
        measurement: symbol graphics only; excludes pins, properties, and text
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    pin_name: ROW6/K4
  - reference: U2
    pin_number: P$2
    pin_name: COM0/AD
  - reference: U2
    pin_number: P$20
    pin_name: ROW5/K3
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    pin_name: ROW0/A2
  - reference: U2
    pin_number: P$3
    pin_name: COM1/KS0
  - reference: U2
    pin_number: P$4
    pin_name: COM2/KS1
  - reference: U2
    pin_number: P$5
    pin_name: COM3/KS2
  - reference: U2
    pin_number: P$6
    pin_name: COM4
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

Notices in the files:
parts and their libraries:
microbuilder-pi: This work is placed in the public domain, and may be freely used for commercial and non-commercial work with the following conditions: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
